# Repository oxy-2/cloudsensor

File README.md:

# cloud
a small fully hardware (as in no firmware needs to be flashed) humidity sensor, sporting a HR202L resistive humidity sensor and a log amp to make it readable along side a dc to ac configurable generator to power the humidity sensor.

everything works on this humidity sensing like device, idk what the proper name is ill just say sensor, everything works on this sensor through the HR202L, but it cant run on DC, it will die because of how resistive humidity sensors work, but it is very accurate from what i know and very nice as a relative humidity sensor, anyways so this full sensor board needs abt 5 diff types of resistors, some to cut down the voltage to the HR202L and then another to set the frequency of the LTC1799 which is providing the AC for the HR202L, then we have a AD8307ANZ to turn the HR202L resistance value into something more usable and then from all of that is given a signal pin for a voltmeter, you can see the pin holes by J2 on the render image at the top.

anyways so other than that for the tools i used, i used kicad and then for like the start i used tinkercad's circuit thing when i was still thinking of using a 555 and trying to figure out how it worked anyways so also credit to google ai at the start tho all it was was the ai overview and search thing, and it lowk sucked and was just telling me random shit, anyways so after i switched to deepseek everything was good and it helped me with component selection and also the schematics, tho i did all the pcb wiring myself and i always do as its calming for me, anyways heres all the images <3

the main goal of this project was to ship for hackclub embassy, also if i build one its lowk just gonna be for my 3d printers diy drybox so i can check humidity levels.

made with love.
by oxy <3

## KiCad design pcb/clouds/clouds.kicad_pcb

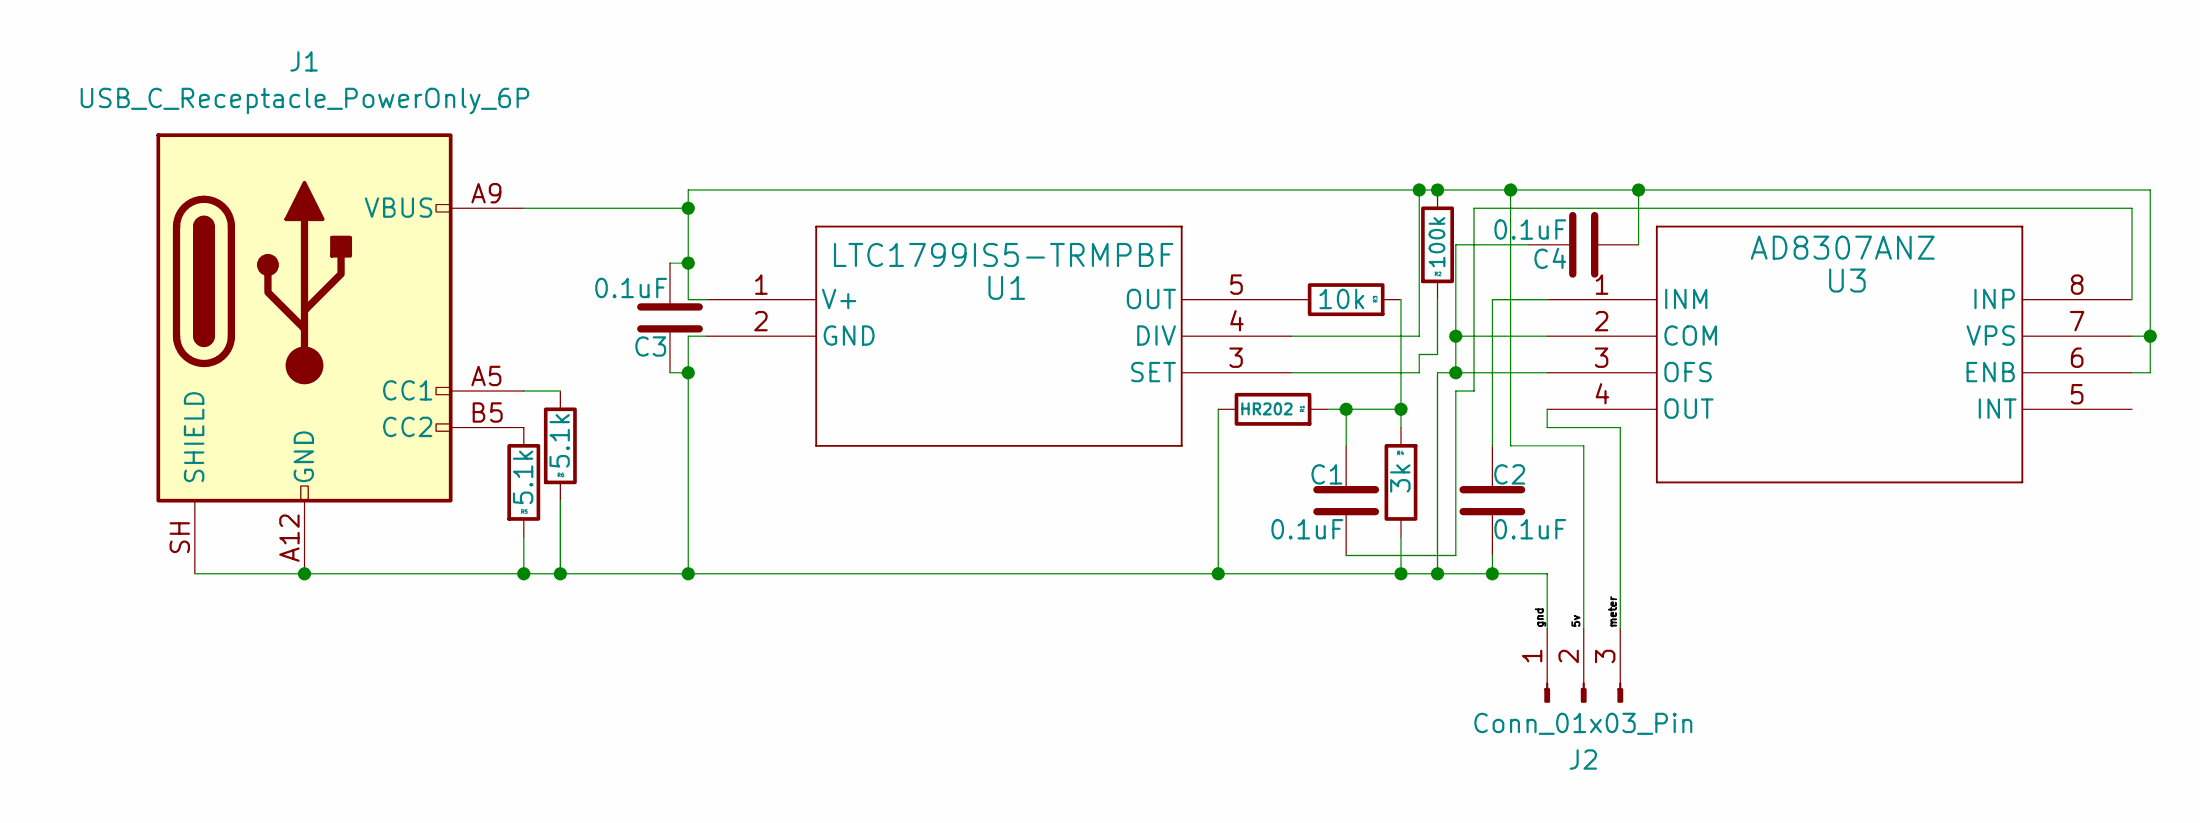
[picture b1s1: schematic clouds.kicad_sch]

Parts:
C1, C2, C3, C4: 0.1uF; C_0201_0603Metric_Pad0.64x0.40mm_HandSolder
J1: USB_C_Receptacle_PowerOnly_6P; USB_C_Receptacle_GCT_USB4125-xx-x_6P_TopMnt_Horizontal
J2: Conn_01x03_Pin; PinHeader_1x03_P2.54mm_Vertical
R1: HR202; R_Axial_DIN0204_L3.6mm_D1.6mm_P2.54mm_Vertical
R2: 100k; R_0201_0603Metric_Pad0.64x0.40mm_HandSolder
R3: 10k; R_0201_0603Metric_Pad0.64x0.40mm_HandSolder
R4: 3k; R_0201_0603Metric_Pad0.64x0.40mm_HandSolder
R5, R6: 5.1k; R_0201_0603Metric_Pad0.64x0.40mm_HandSolder
U1: LTC1799IS5-TRMPBF; S5_05-08-1635_ADI-M
U3: AD8307ANZ; N_8_ADI

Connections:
/5v: C3.2, C4.2, J1.A9 (VBUS), J1.B9 (VBUS), J2.2, R2.1, U1.1 (V+), U1.4 (DIV), U3.6 (ENB), U3.7 (VPS)
/gnd: C2.1, C3.1, C4.1, J1.A12 (GND), J1.B12 (GND), J1.SH (SHIELD), J2.1, R1.1, R4.1, R5.2, R6.2, U1.2 (GND), U3.2 (COM), U3.3 (OFS)
/meter: J2.3, U3.4 (OUT)
unnamed: C1.2, R1.2, R3.2, R4.2
unnamed: J1.A5 (CC1), R6.1
unnamed: J1.B5 (CC2), R5.1
unnamed: R3.1, U1.5 (OUT)
unnamed: R2.2, U1.3 (SET)
unnamed: C2.2, U3.1 (INM)
unnamed: C1.1, U3.8 (INP)

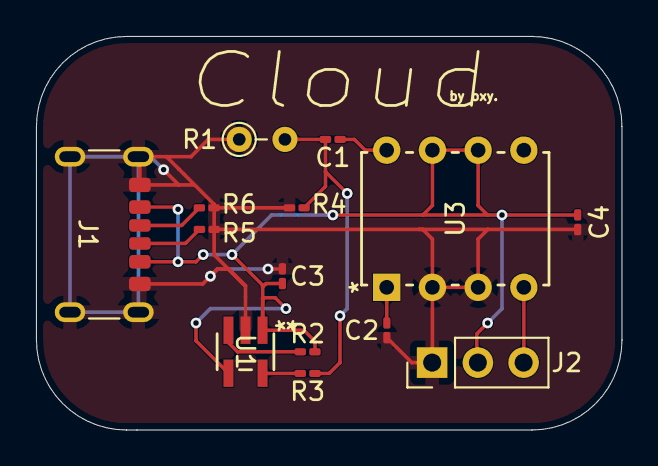
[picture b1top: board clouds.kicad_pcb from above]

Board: 2 copper layers, 32.5 x 21.9 mm, 14 parts (0 on the bottom side), 10 nets.

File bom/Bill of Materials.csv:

item,selection,price per unit,quantity,source
aliexpress:,,,,
0.28 inch DC 0-100V 3-Wire Mini Gauge voltage meter Voltmeter LED Display Digital Panel Voltmeter Meter Detector Monitor Tools,3 line Blue,"1,94€",1,https://pt.aliexpress.com/item/32721355971.html?spm=a2g0o.pr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
100pcs 1% 0603 SMD resistor 0R ~ 10M 1/10W 0.1 1 10 47 100 150 220 330 ohm 1K 2.2K 10K 100K 0.1R 1R 10R 100R 150R 220R 330R 1M,Resistance: 5.1K,"0,75€",1,https://pt.aliexpress.com/item/1005011982912733.html?spm=a2g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
100pcs 1% 0603 SMD resistor 0R ~ 10M 1/10W 0.1 1 10 47 100 150 220 330 ohm 1K 2.2K 10K 100K 0.1R 1R 10R 100R 150R 220R 330R 1M,Resistance: 3K,"0,75€",1,https://pt.aliexpress.com/item/1005011982912733.html?spm=a2g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
100pcs 1% 0603 SMD resistor 0R ~ 10M 1/10W 0.1 1 10 47 100 150 220 330 ohm 1K 2.2K 10K 100K 0.1R 1R 10R 100R 150R 220R 330R 1M,Resistance: 10K,"0,75€",1,https://pt.aliexpress.com/item/1005011982912733.html?spm=a2g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
100pcs 1% 0603 SMD resistor 0R ~ 10M 1/10W 0.1 1 10 47 100 150 220 330 ohm 1K 2.2K 10K 100K 0.1R 1R 10R 100R 150R 220R 330R 1M,Resistance: 100K,"0,75€",1,https://pt.aliexpress.com/item/1005011982912733.html?spm=a2g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
100pcs/lot SMD Ceramic Capacitor 0201 0402 0603 0805 1206 100nF 220nF 330nF 470nF 680nF 0.1uF 0.22uF 0.47uF 0.68uF X7R 10% 50V,Capacitance: 0603 100nF 25V X7R,"2,02€/lot",1,https://pt.aliexpress.com/item/1005012005178799.html?spm=a2g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
1pcs CJ-HR31 HR202 HR202L Humidity Sensor Humidity Resistance,Color: HR202L with case,"1,90€",,https://pt.aliexpress.com/item/1005005986773078.html?spm=a2g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
AD620ANZ AD622ANZ AD623ANZ AD627ANZ AD629ANZ AD797ANZ AD820ANZ AD822ANZ AD8307ANZ AD844ANZ AD8561ANZ PC shell,Color: AD8307ANZ,"9,99€",1,https://pt.aliexpress.com/item/1005013352312609.html?spm=a2g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
chip chip Integrated circuit chip MCU chip LTC1799IS5#TRMPBF LTC6905IS5-80#TRPBF LTC6995IS6-2#TRMPBF LTC6930IMS8-8.00#PBF,Color: LTC1799IS5 TRMPBF,"5,73€",1,https://pt.aliexpress.com/item/1005012883792458.html?spm=a2g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
20/10/5pcs 6 Pin SMT Socket Connector Micro USB Type C 3.1 Female Placement SMD DIP For PCB design DIY high current charging,Package Quantity: 5PCS,"1,86€",1,https://pt.aliexpress.com/item/1005006047551075.html?spm=a2g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
,,,,
"total sourced: 26,44 €",,,,
